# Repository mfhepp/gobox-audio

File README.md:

# Audio Amplifier and Zero Beat Indicator for QRP Transceivers
This projects contains the necessary files and assembly instructions for a small PCB that includes a
a) LM386-based audio amplifier and a
b) LMC567-based zero beat indicator.

The board was designed for the [Mountain Topper SOTA GoBox](https://github.com/mfhepp/gobox) project, but can be used for any other similar project.

The LM386 amplifier is carefully tuned to operate in RF-noisy environments, as typical for amateur radio transceivers. For that purpose, it includes several additional filter components not found in the mainstream datasheet applications.

Design decisions will also be included in the final version.

**Note:** This is work-in-progress. I will remove this message when the materials are ready for use.

## Overview 
tbd

## Part List
tbd

## Assembly
tbd

## Calibration
tbd

## Sources
The files in the repository contain 
* Gerber and drill files for producing your own PCBs, and
* a KiCad project with the schematics, PCB, and parts and footprints libraries.

KiCad is a great and free electronics design package. For more information, see [http://kicad-pcb.org/](http://kicad-pcb.org/).

## Acknowledgments
tbd

## Disclaimer 
THE SOFTWARE AND DESIGN ARE PROVIDED "AS IS", WITHOUT WARRANTY OF ANY KIND, EXPRESS OR IMPLIED, INCLUDING BUT NOT LIMITED TO THE WARRANTIES OF MERCHANTABILITY, FITNESS FOR A PARTICULAR PURPOSE AND NONINFRINGEMENT. IN NO EVENT SHALL THE AUTHORS OR COPYRIGHT HOLDERS BE LIABLE FOR ANY CLAIM, DAMAGES OR OTHER LIABILITY, WHETHER IN AN ACTION OF CONTRACT, TORT OR OTHERWISE, ARISING FROM, OUT OF OR IN CONNECTION WITH THE SOFTWARE OR DESIGN OR THE USE OR OTHER DEALINGS IN THE SOFTWARE OR DESIGN.

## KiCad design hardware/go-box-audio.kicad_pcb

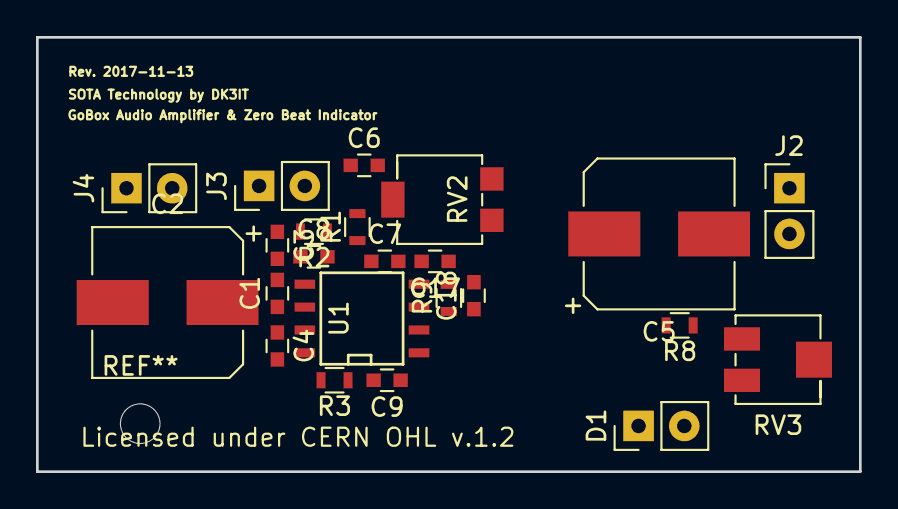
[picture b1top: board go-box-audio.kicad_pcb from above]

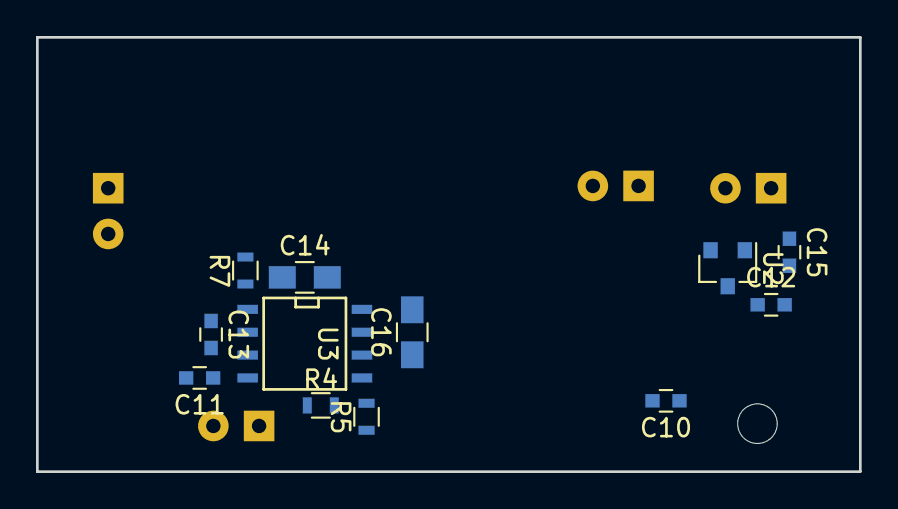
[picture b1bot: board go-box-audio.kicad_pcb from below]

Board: 2 copper layers, 45.7 x 24.1 mm, 38 parts (12 on the bottom side), 24 nets, no tracks yet.

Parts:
C1, C8, C13: 100n; C_0603
C2, C5: 100u/16..25V; CP_Elec_8x6.7
C3: 10n; C_0603
C4, C9, C12: 10u/16V; C_0603
C6, C17: 470n; C_0603
C7, C18: 1n; C_0603
C10, C11, C15: 2.2u; C_0603
C14: 1u X7R; C_0805_HandSoldering
C16: 47n U2J; C_0805_HandSoldering
D1: ZERO_BEAT (blue); Generic_2-Pin_Connector_0.8mm
J1: EARPHONE; not_on_board
J2: Speaker 8R/0.5W; Generic_2-Pin_Connector_0.8mm
J3: RIG_AF; Generic_2-Pin_Connector_0.8mm
J4: RIG_VCC; Generic_2-Pin_Connector_0.8mm
J5: RIG_AF_OUT; not_on_board
R1, R9: 680; R_0603
R2: 10; R_0603
R3: 1.8k; R_0603
R4: 22k; R_0603
R5: 180; R_0603
R7: 390k; R_0603
R8: 4.7k; R_0603
RV1: 1k; not_on_board
RV2: 10k; Potentiometer_Trimmer_Bourns_3314G
RV3: 20k; Potentiometer_Trimmer_Bourns_3214J
U1: LM386M-1; SOIC-8-N
U2: LM3480-5.0; SOT-23
U3: LMC567; SOIC-8-N

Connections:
AF_IN: C3.1, C6.1, C13.1, J3.2
GND: C1.2, C2.2, C3.2, C4.2, C7.2, C10.2, C11.2, C12.2, C14.2, C15.2, C16.2, C17.2, C18.2, J2.1, J3.1, J4.1, R2.2, R7.2, RV2.3, U1.4, U2.3, U3.7
unnamed: C4.1, U1.7
unnamed: C5.1, C8.1, U1.5
unnamed: C5.2, J2.2
unnamed: C6.2, RV2.1
unnamed: C7.1, R1.1, U1.3
unnamed: C8.2, R2.1
unnamed: C9.1, U1.1
unnamed: C9.2, R3.1
unnamed: C11.1, C12.1, D1.2, R4.1, U2.1, U3.4
unnamed: C13.2, U3.3
unnamed: C14.1, U3.2
unnamed: C15.1, R7.1, U3.1
unnamed: C16.1, R8.2, U3.6
unnamed: C17.1, R9.2
unnamed: C18.1, R9.1, U1.2
unnamed: D1.1, R5.1
unnamed: R1.2, RV2.2
unnamed: R3.2, U1.8
unnamed: R4.2, R5.2, U3.8
unnamed: R8.1, RV3.3
unnamed: RV3.1, RV3.2, U3.5
RIG_VCC: C1.1, C2.1, C10.1, J4.2, U1.6, U2.2

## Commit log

2017-11-14 added README.md

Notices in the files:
hardware/go-box-audio.kicad_pcb:
Licensed under CERN OHL v.1.2
